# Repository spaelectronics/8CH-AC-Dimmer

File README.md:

# 8CH-AC-Dimmer
8 Channel A/C Dimmer w/Zero Cross Detection. Designed for use with Christmas Lights. Works with Vixen V2.

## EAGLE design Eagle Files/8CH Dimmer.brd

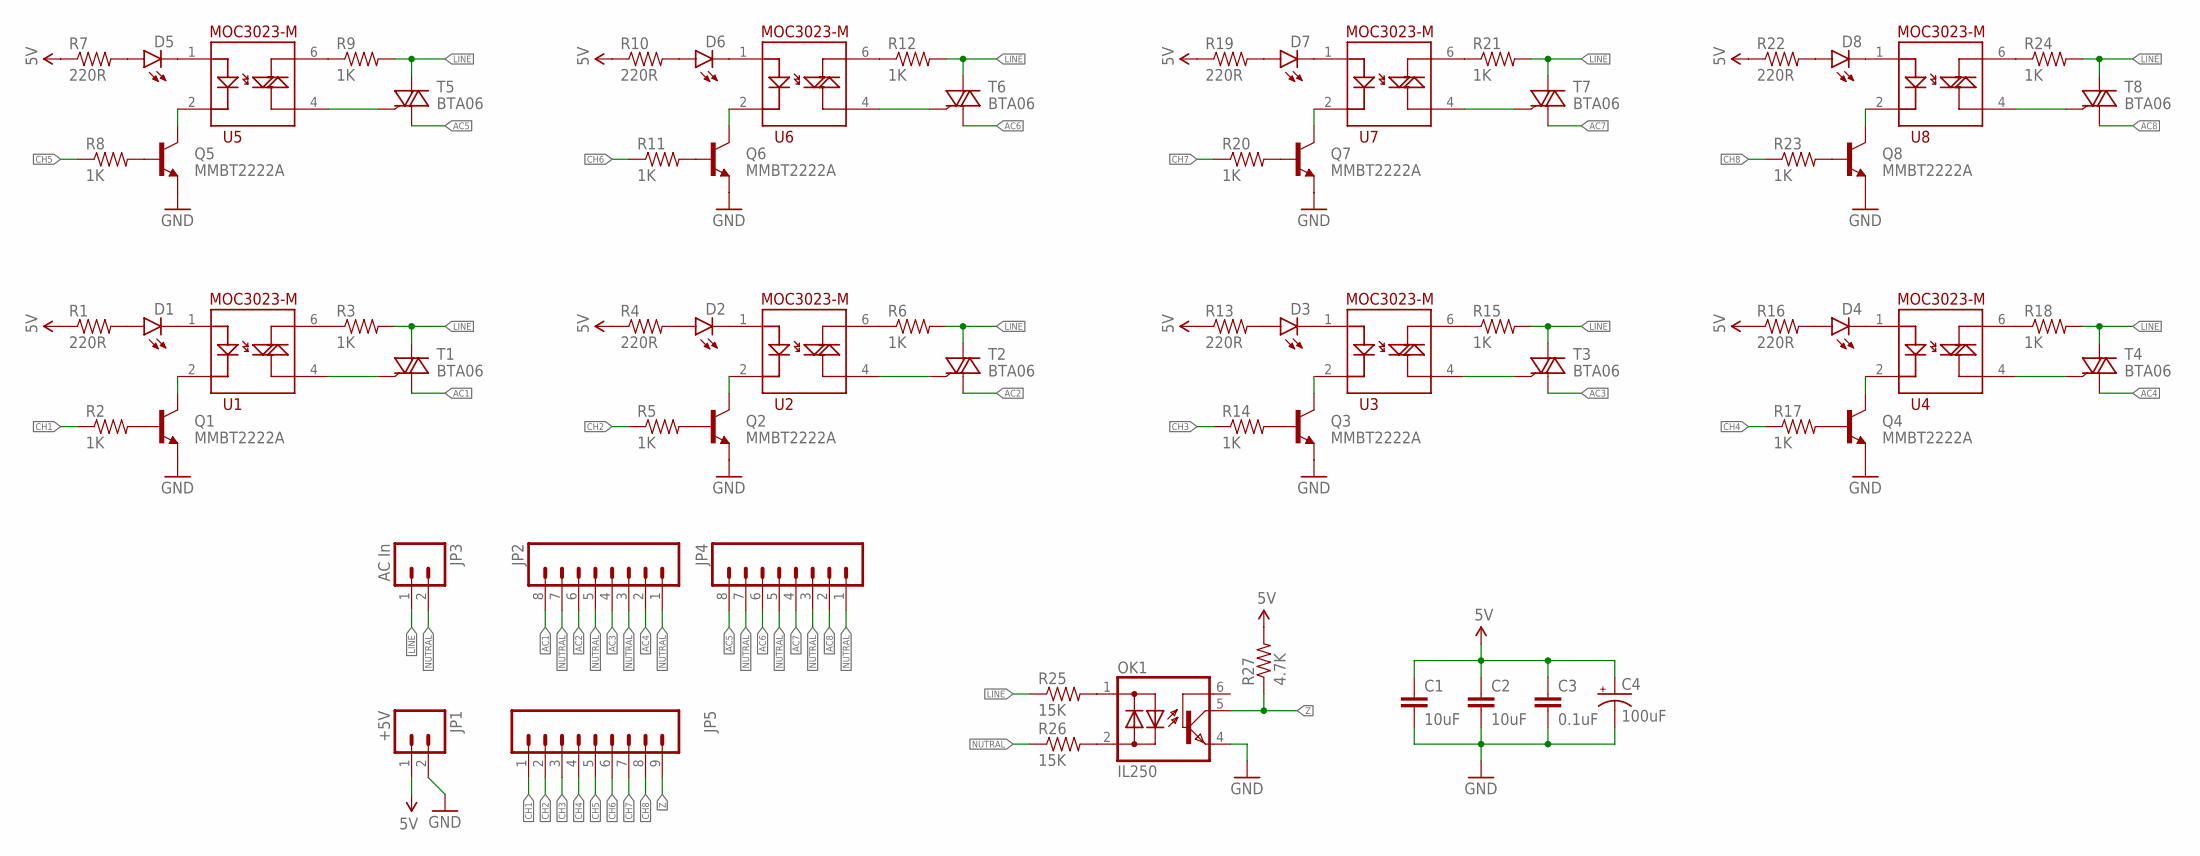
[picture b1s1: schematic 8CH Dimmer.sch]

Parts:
C1, C2: 10uF; 0805
C3: 0.1uF; 0805
C4: 100uF; E2,5-5
D1, D2, D3, D4, D5, D6, D7, D8: LED3MM
JP1: +5V; SCREWTERMINAL-3.5MM-2
JP2, JP4: M083.5MM-8; SCREWTERMINAL-3.5MM-8
JP3: AC In; SCREWTERMINAL-3.5MM-2
JP5: M09; 1X09
OK1: IL250; DIL06
Q1, Q2, Q3, Q4, Q5, Q6, Q7, Q8: MMBT2222A; SOT23-3
R1, R4, R7, R10, R13, R16, R19, R22: 220R; 0805
R2, R5, R8, R11, R14, R17, R20, R23: 1K; 0805
R3, R6, R9, R12, R15, R18, R21, R24: 1K; AXIAL-0.5
R25, R26: 15K; AXIAL-0.5
R27: 4.7K; 0805
T1, T2, T3, T4, T5, T6, T7, T8: BTA06; TO220-V
U1, U2, U3, U4, U5, U6, U7, U8: MOC3023-M; DIL06

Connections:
5V: C1.1, C2.1, C3.1, C4.+, JP1.1, R1.1, R4.1, R7.1, R10.1, R13.1, R16.1, R19.1, R22.1, R27.2
AC1: JP2.8, T1.1 (A1)
AC2: JP2.6, T2.1 (A1)
AC3: JP2.4, T3.1 (A1)
AC4: JP2.2, T4.1 (A1)
AC5: JP4.8, T5.1 (A1)
AC6: JP4.6, T6.1 (A1)
AC7: JP4.4, T7.1 (A1)
AC8: JP4.2, T8.1 (A1)
CH1: JP5.1, R2.1
CH2: JP5.2, R5.1
CH3: JP5.3, R14.1
CH4: JP5.4, R17.1
CH5: JP5.5, R8.1
CH6: JP5.6, R11.1
CH7: JP5.7, R20.1
CH8: JP5.8, R23.1
GND: C1.2, C2.2, C3.2, C4.-, JP1.2, OK1.4 (E), Q1.2 (E), Q2.2 (E), Q3.2 (E), Q4.2 (E), Q5.2 (E), Q6.2 (E), Q7.2 (E), Q8.2 (E)
LINE: JP3.1, R3.P$2 (2), R6.P$2 (2), R9.P$2 (2), R12.P$2 (2), R15.P$2 (2), R18.P$2 (2), R21.P$2 (2), R24.P$2 (2), R25.P$1 (1), T1.2 (A2), T2.2 (A2), T3.2 (A2), T4.2 (A2), T5.2 (A2), T6.2 (A2), T7.2 (A2), T8.2 (A2)
unnamed: D1.K (C), U1.1
unnamed: D1.A, R1.2
unnamed: Q1.1 (B), R2.2
unnamed: T1.3 (G), U1.4
unnamed: Q1.3 (C), U1.2
unnamed: R3.P$1 (1), U1.6
unnamed: Q2.1 (B), R5.2
unnamed: T2.3 (G), U2.4
unnamed: R6.P$1 (1), U2.6
unnamed: Q2.3 (C), U2.2
unnamed: D2.K (C), U2.1
unnamed: D2.A, R4.2
unnamed: Q5.1 (B), R8.2
unnamed: T5.3 (G), U5.4
unnamed: R9.P$1 (1), U5.6
unnamed: Q5.3 (C), U5.2
unnamed: D5.K (C), U5.1
unnamed: D5.A, R7.2
unnamed: Q6.1 (B), R11.2
unnamed: T6.3 (G), U6.4
unnamed: R12.P$1 (1), U6.6
unnamed: Q6.3 (C), U6.2
unnamed: D6.K (C), U6.1
unnamed: D6.A, R10.2
unnamed: Q3.1 (B), R14.2
unnamed: T3.3 (G), U3.4
unnamed: R15.P$1 (1), U3.6
unnamed: Q3.3 (C), U3.2
unnamed: D3.K (C), U3.1
unnamed: D3.A, R13.2
unnamed: Q4.1 (B), R17.2
unnamed: T4.3 (G), U4.4
unnamed: R18.P$1 (1), U4.6
unnamed: Q4.3 (C), U4.2
unnamed: D4.K (C), U4.1
unnamed: D4.A, R16.2
unnamed: Q7.1 (B), R20.2
unnamed: T7.3 (G), U7.4
unnamed: R21.P$1 (1), U7.6
unnamed: Q7.3 (C), U7.2
unnamed: D7.K (C), U7.1
unnamed: D7.A, R19.2
unnamed: Q8.1 (B), R23.2
unnamed: T8.3 (G), U8.4
unnamed: R24.P$1 (1), U8.6
unnamed: Q8.3 (C), U8.2
unnamed: D8.K (C), U8.1
unnamed: D8.A, R22.2
unnamed: OK1.1 (AC1), R25.P$2 (2)
unnamed: OK1.2 (AC2), R26.P$2 (2)
NUTRAL: JP2.1, JP2.3, JP2.5, JP2.7, JP3.2, JP4.1, JP4.3, JP4.5, JP4.7, R26.P$1 (1)
Z: JP5.9, OK1.5 (C), R27.1

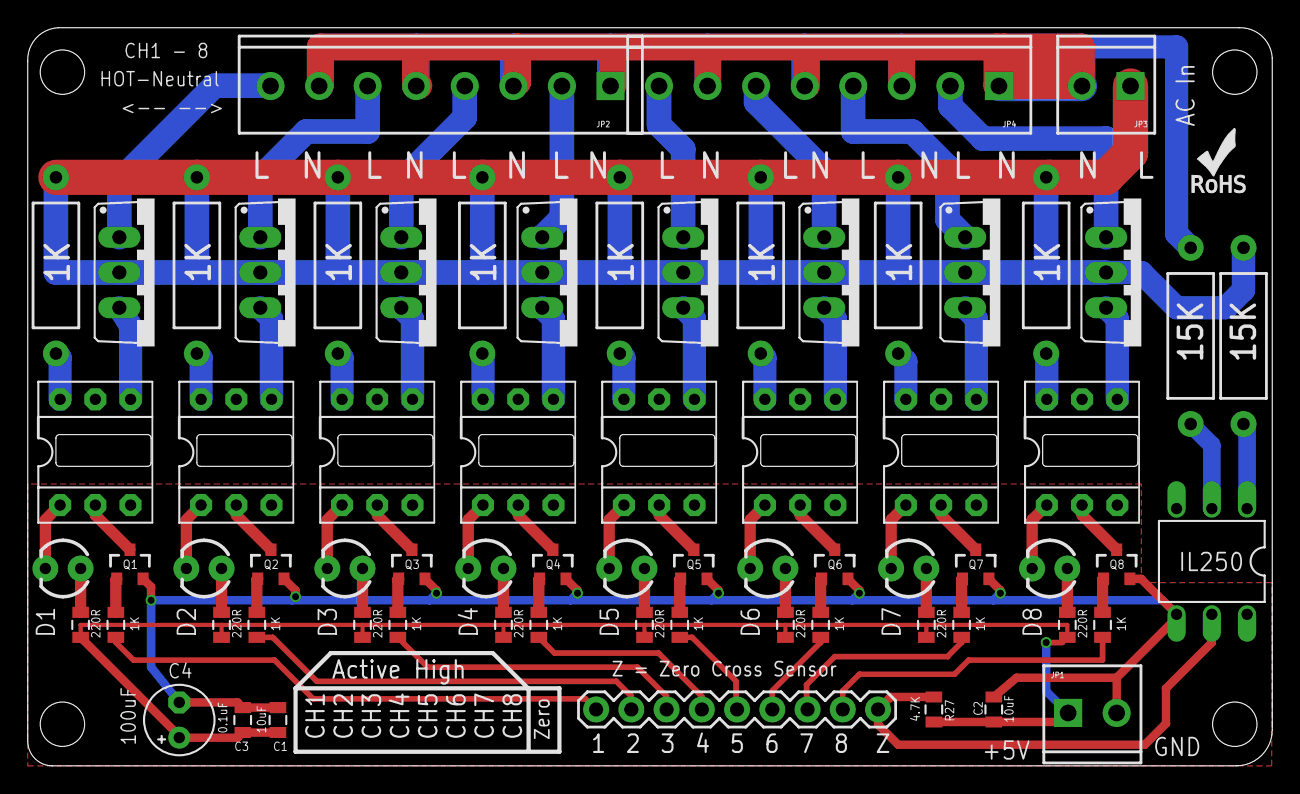
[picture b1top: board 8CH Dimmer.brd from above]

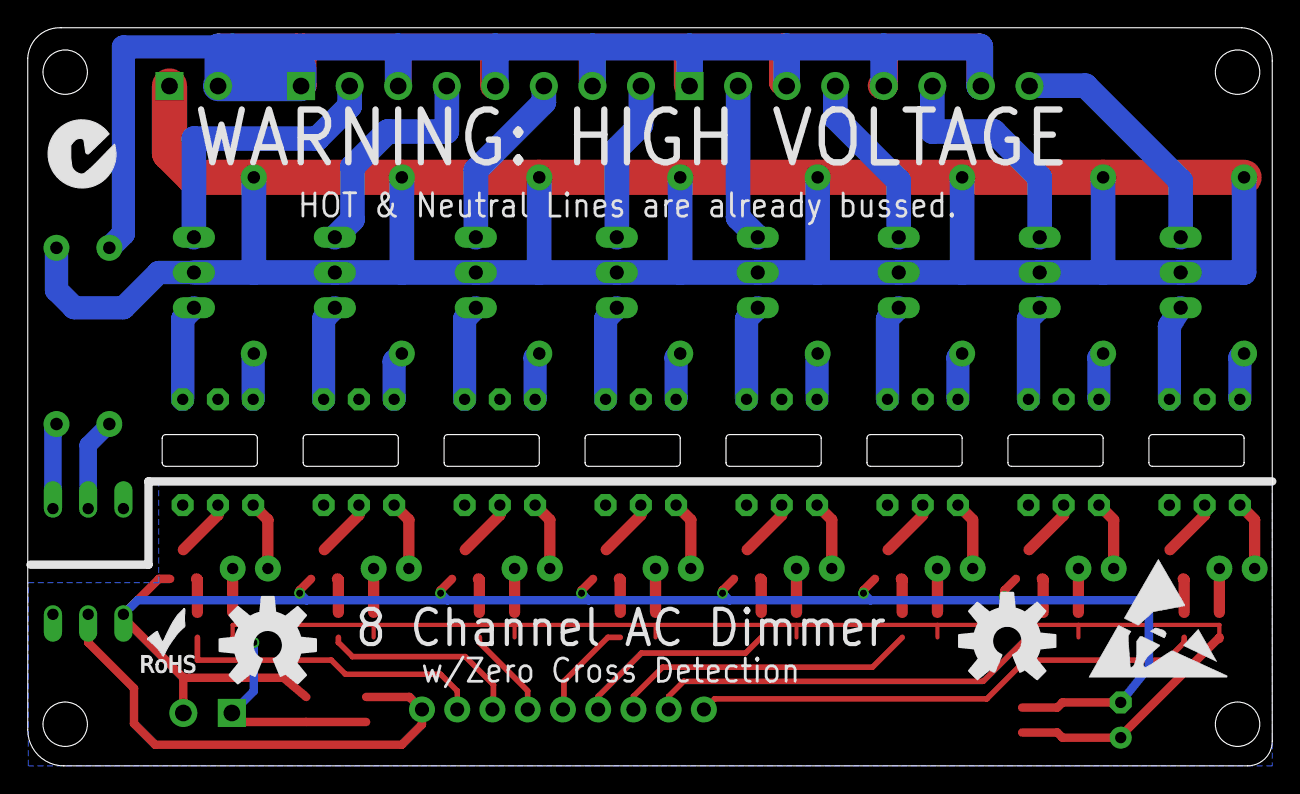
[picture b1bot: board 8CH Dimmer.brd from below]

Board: 2 copper layers, 89.7 x 53.2 mm, 75 parts (5 on the bottom side), 71 nets.

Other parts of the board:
U$1, U$2: OSHW-LOGO-L
U$3, U$4: ROHS_LOGO_0.18_IN
U$5: C_TICK-5MM
U$6: ESD_10.00

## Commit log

2018-09-07 Add Files

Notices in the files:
parts and their libraries:
SparkFun-Capacitors: Licensing: Creative Commons ShareAlike 4.0 International - https://creativecommons.org/licenses/by-sa/4.0
